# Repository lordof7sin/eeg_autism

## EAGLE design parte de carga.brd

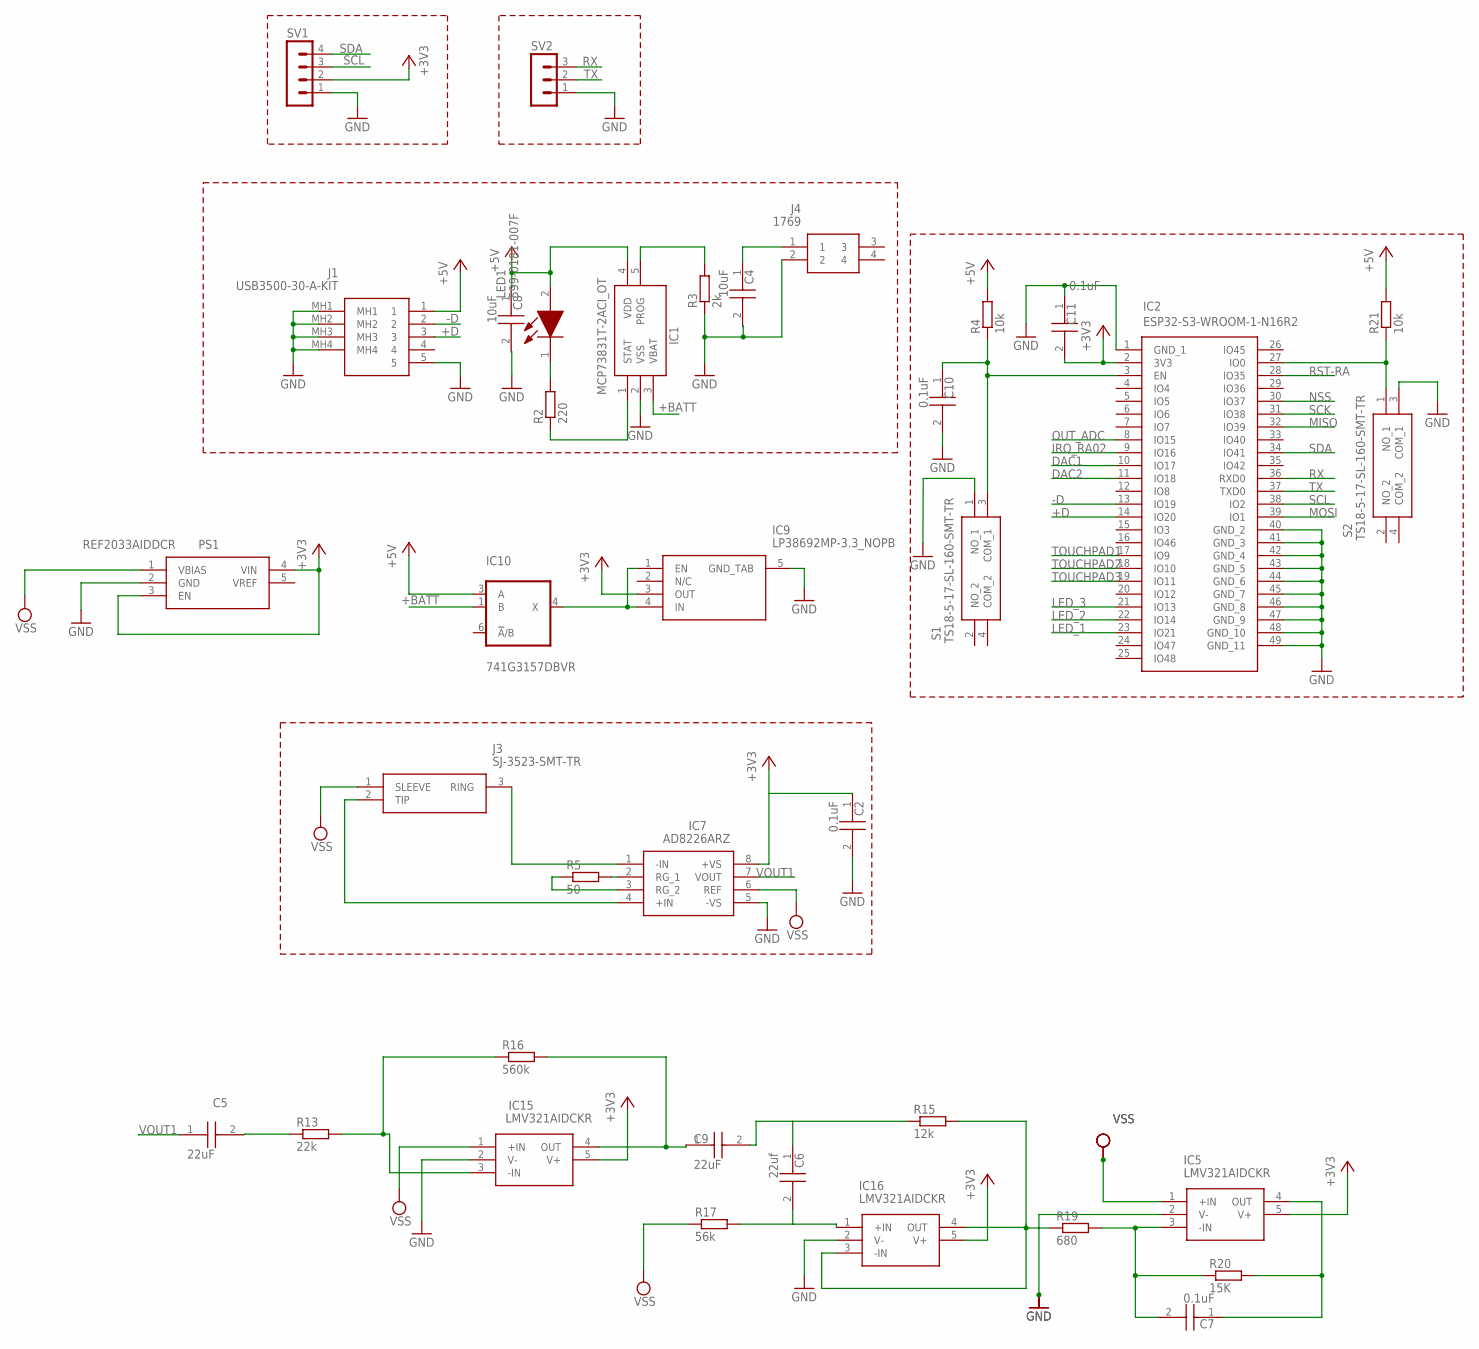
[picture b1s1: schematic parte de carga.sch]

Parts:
C2, C7, C10, C11: 0.1uF; CAPC2012X140N
C4, C8: 10uF; CAPC2012X140N
C5, C9: 22uF; CAPC2012X140N
C6: 22uf; CAPC2012X140N
IC1: MCP73831T-2ACI_OT; SOT95P270X145-5N
IC2: ESP32-S3-WROOM-1-N16R2; ESP32S3WROOM1N16R2
IC5, IC15, IC16: LMV321AIDCKR; SOT65P210X110-5N
IC7: AD8226ARZ; SOIC127P600X175-8N
IC9: LP38692MP-3.3_NOPB; SOT150P700X180-5N
IC10: 741G3157DBVR; DBV_R-PDSO-G6
J1: USB3500-30-A-KIT; USB350030AKIT
J3: SJ-3523-SMT-TR; SJ3523SMTTR
J4: 1769
LED1: 599-0181-007F; LEDC2012X70N
PS1: REF2033AIDDCR; SOT95P280X110-5N
R2: 220; R0805
R3: 2k; R0805
R4, R21: 10k; R0805
R5: 50; R0805
R13: 22k; R0805
R15: 12k; R0805
R16: 560k; R0805
R17: 56k; R0805
R19: 680; R0805
R20: 15K; R0805
S1, S2: TS18-5-17-SL-160-SMT-TR; TS18517SL160SMTTR
SV1: MA04-1
SV2: MA03-1

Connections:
+3V3: C2.1, C11.2, IC2.2 (3V3), IC5.5 (V+), IC7.8 (+VS), IC9.3 (OUT), IC15.5 (V+), IC16.5 (V+), PS1.3 (EN), PS1.4 (VIN), SV1.2
+5V: C8.1, IC1.4 (VDD), IC10.3 (A), J1.1, LED1.2 (A), R4.2, R21.2
+BATT: IC1.3 (VBAT)
+D: IC2.14 (IO20), J1.3
-D: IC2.13 (IO19), J1.2
DAC1: IC2.10 (IO17)
DAC2: IC2.11 (IO18)
GND: C2.2, C4.2, C8.2, C10.2, C11.1, IC1.2 (VSS), IC2.1 (GND_1), IC2.40 (GND_2), IC2.41 (GND_3), IC2.42 (GND_4), IC2.43 (GND_5), IC2.44 (GND_6), IC2.45 (GND_7), IC2.46 (GND_8), IC2.47 (GND_9), IC2.48 (GND_10), IC2.49 (GND_11), IC5.2 (V-), IC7.5 (-VS), IC9.5 (GND_TAB), IC10.2 (GND), IC15.2 (V-), IC16.2 (V-), J1.5, J1.MH1, J1.MH2, J1.MH3, J1.MH4, J4.2, R3.1, S1.1 (NO_1), S2.3 (COM_1), SV1.1, SV2.1
IRQ_RA02: IC2.9 (IO16)
LED_1: IC2.23 (IO21)
LED_2: IC2.22 (IO14)
LED_3: IC2.21 (IO13)
MISO: IC2.32 (IO39)
MOSI: IC2.39 (IO1)
unnamed: IC1.1 (STAT), R2.1
unnamed: LED1.1 (K), R2.2
unnamed: IC1.5 (PROG), R3.2
unnamed: C10.1, IC2.3 (EN), R4.1, S1.3 (COM_1)
unnamed: IC2.27 (IO0), PS1.2 (GND), R21.1, S2.1 (NO_1)
unnamed: IC16.3 (-IN), IC16.4 (OUT), R15.2, R19.1
unnamed: C7.1, IC5.4 (OUT), R20.2
unnamed: C7.2, IC5.3 (-IN), R19.2, R20.1
unnamed: IC7.2 (RG_1), R5.2
unnamed: IC7.1 (-IN), J3.3 (RING)
unnamed: IC7.3 (RG_2), R5.1
unnamed: C6.2, IC16.1 (+IN), R17.2
unnamed: C5.2, R13.1
unnamed: IC7.4 (+IN), J3.2 (TIP)
unnamed: C6.1, C9.2, R15.1
unnamed: C4.1, J4.1
unnamed: IC9.1 (EN), IC9.4 (IN), IC10.4 (X)
unnamed: IC15.3 (-IN), R13.2, R16.1
unnamed: C9.1, IC15.4 (OUT), R16.2
NSS: IC2.30 (IO37)
OUT_ADC: IC2.8 (IO15)
RST-RA: IC2.28 (IO35)
RX: IC2.36 (RXD0), SV2.3
SCK: IC2.31 (IO38)
SCL: IC2.38 (IO2), SV1.3
SDA: IC2.34 (IO41), SV1.4
TOUCHPAD1: IC2.17 (IO9)
TOUCHPAD2: IC2.18 (IO10)
TOUCHPAD3: IC2.19 (IO11)
TX: IC2.37 (TXD0), SV2.2
VCC: IC10.5 (VCC)
VOUT1: C5.1, IC7.7 (VOUT)
VSS: IC5.1 (+IN), IC7.6 (REF), IC15.1 (+IN), J3.1 (SLEEVE), PS1.1 (VBIAS), R17.1

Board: 2 copper layers, 37 parts (0 on the bottom side), 30 nets, no tracks yet.

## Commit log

2025-04-04 proyecto iniciado
2025-04-04 Correcciones del profesor
2025-04-11 cambie resistencias y condensadores
2025-04-12 Cambie las fuentes y algunos valores a las resistencias
2025-04-23 cree el espacio para la pcb falta organizarla
2025-04-28 cambie la escala del esquematico
2025-04-28 arregle las resistencias, condensadores y diodo
2025-05-02 ya agregue las capas de gnd falta que arreglen los componentes
2025-05-02 acomode componentes en la board Harold Astudillo
2025-05-05 areglé parte del puerto usb, y el conector de elctrodos, saqué un conector de 3 pines rx. tx, gnd. saqué un conector para el display
2025-05-06 Corregir huellas capacitores, organice esp32 y Amp Op
2025-05-06 Astudillo estuvo aqui
2025-05-07 acomode los compenentes dentro de la placa falta organizarlos y elimine una parte de los filtros que no estaba amplificando nada
